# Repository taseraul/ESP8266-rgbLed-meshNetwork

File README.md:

# ESP8266-rgbLed-meshNetwork
Controller for RGB LED Strips linked in mesh network with ESP-Now protocol

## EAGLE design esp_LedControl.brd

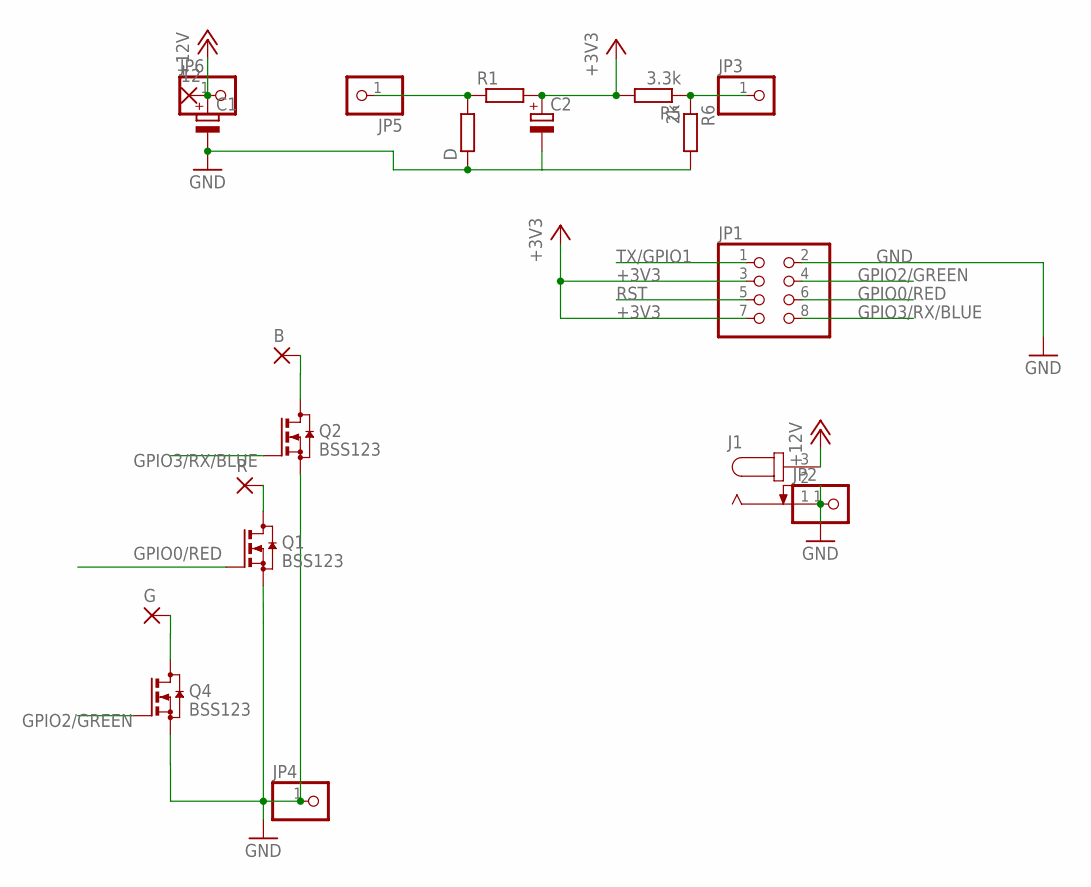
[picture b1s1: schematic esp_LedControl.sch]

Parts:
12: 3,17/1,3
B: 3,17/1,3
C1, C2: CPOL-EUE2.5-5; E2,5-5
D: R-EU_0204/7; 0204/7
G: 3,17/1,3
J1: JACK-PLUG0; SPC4077
JP1: PINHD-2X4; 2X04
JP2, JP3, JP4, JP5, JP6: PINHD-1X1; 1X01
Q1, Q2, Q4: BSS123; SOT23
R: 3,17/1,3
R1: R-EU_0204/7; 0204/7
R5: 3.3k; R0805
R6: 2k; R0805

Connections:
+3V3: C2.+, JP1.3, JP1.7, R1.2, R5.2
+12V: 12.1, C1.+, J1.3, JP6.1
GND: C1.-, C2.-, D.1, J1.1, J1.2, JP1.2, JP2.1, JP4.1, Q1.2 (S), Q2.2 (S), Q4.2 (S), R6.2
GPIO0/RED: JP1.6, Q1.1 (G)
GPIO2/GREEN: JP1.4, Q4.1 (G)
GPIO3/RX/BLUE: JP1.8, Q2.1 (G)
unnamed: G.1, Q4.3 (D)
unnamed: JP3.1, R5.1, R6.1
unnamed: B.1, Q2.3 (D)
unnamed: D.2, JP5.1, R1.1
unnamed: Q1.3 (D), R.1
RST: JP1.5
TX/GPIO1: JP1.1

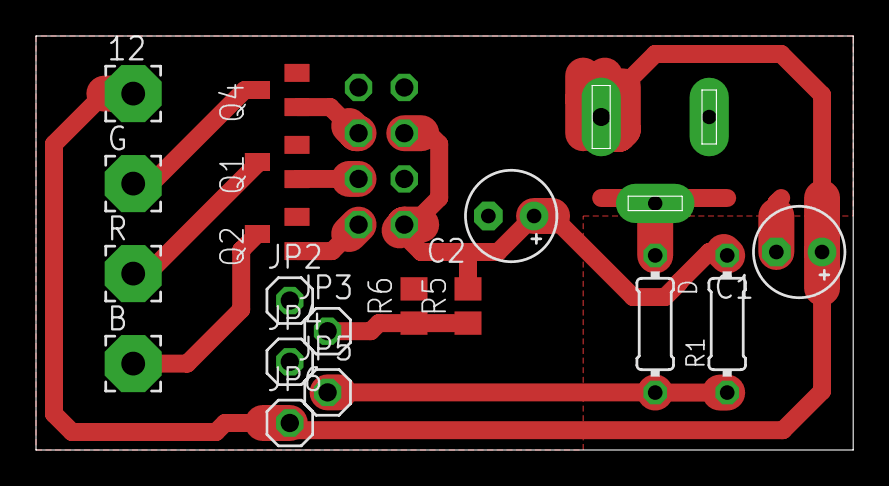
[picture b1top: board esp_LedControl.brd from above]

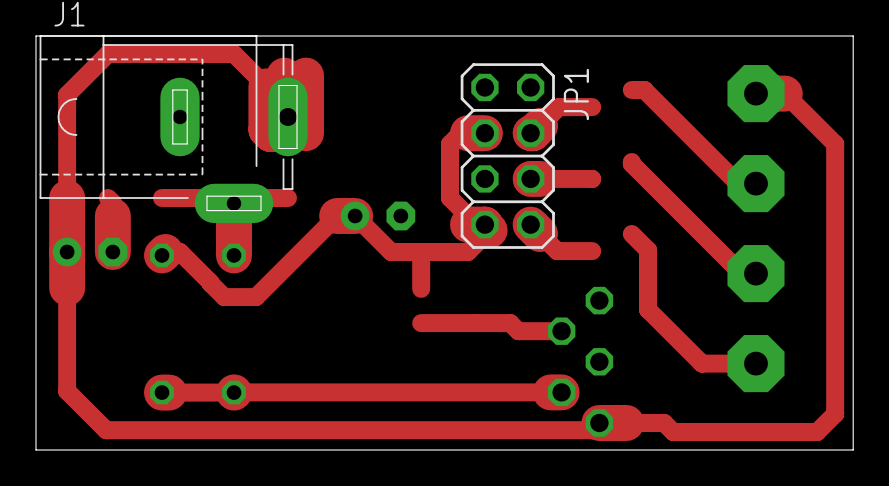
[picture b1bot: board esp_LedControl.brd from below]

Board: 2 copper layers, 45.4 x 23.0 mm, 20 parts (2 on the bottom side), 11 nets.

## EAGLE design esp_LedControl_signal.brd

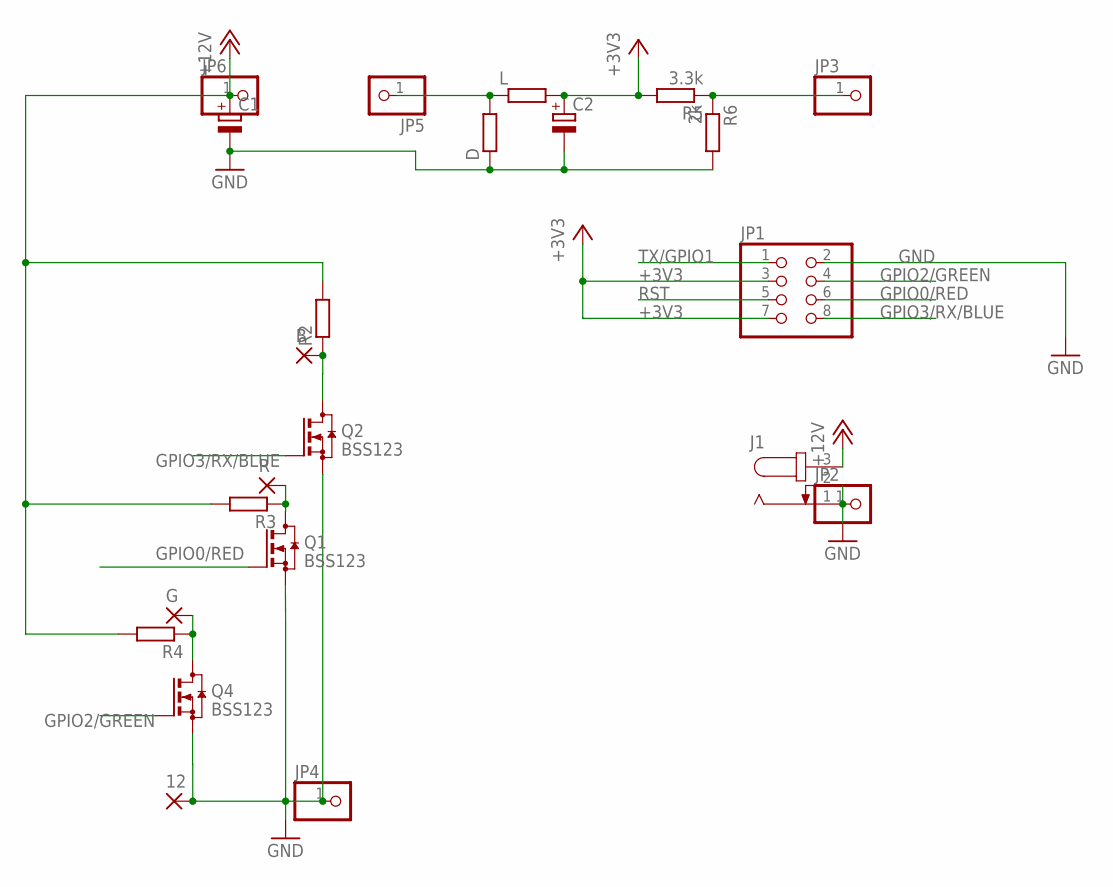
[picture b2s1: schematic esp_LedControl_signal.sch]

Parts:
12: 3,17/1,3
B: 3,17/1,3
C1, C2: CPOL-EUE2.5-5; E2,5-5
D: R-EU_0204/7; 0204/7
G: 3,17/1,3
J1: JACK-PLUG0; SPC4077
JP1: PINHD-2X4; 2X04
JP2, JP3, JP4, JP5, JP6: PINHD-1X1; 1X01
L: R-EU_0204/7; 0204/7
Q1, Q2, Q4: BSS123; SOT23
R: 3,17/1,3
R2, R3, R4: R-EU_R0805; R0805
R5: 3.3k; R1206
R6: 2k; R1206

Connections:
+3V3: C2.+, JP1.3, JP1.7, L.2, R5.2
+12V: C1.+, J1.3, JP6.1, R2.2, R3.2, R4.2
GND: 12.1, C1.-, C2.-, D.1, J1.1, J1.2, JP1.2, JP2.1, JP4.1, Q1.2 (S), Q2.2 (S), Q4.2 (S), R6.2
GPIO0/RED: JP1.6, Q1.1 (G)
GPIO2/GREEN: JP1.4, Q4.1 (G)
GPIO3/RX/BLUE: JP1.8, Q2.1 (G)
unnamed: G.1, Q4.3 (D), R4.1
unnamed: JP3.1, R5.1, R6.1
unnamed: B.1, Q2.3 (D), R2.1
unnamed: D.2, JP5.1, L.1
unnamed: Q1.3 (D), R.1, R3.1
RST: JP1.5
TX/GPIO1: JP1.1

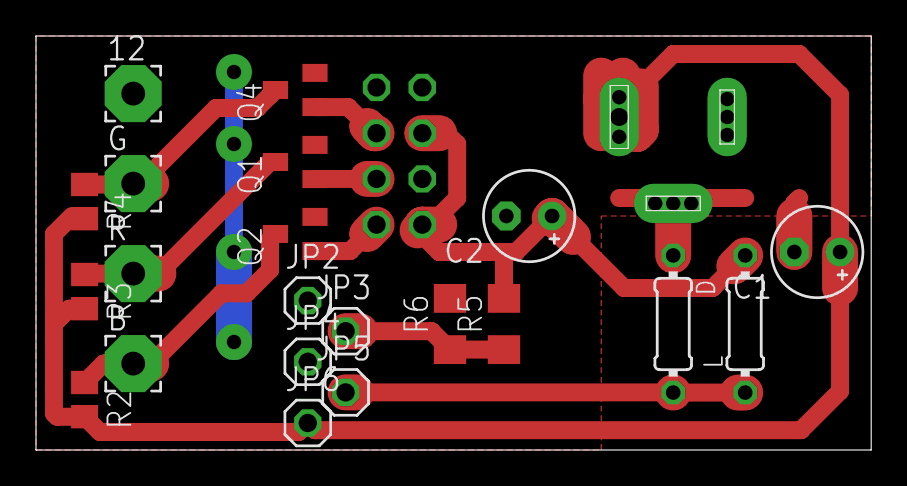
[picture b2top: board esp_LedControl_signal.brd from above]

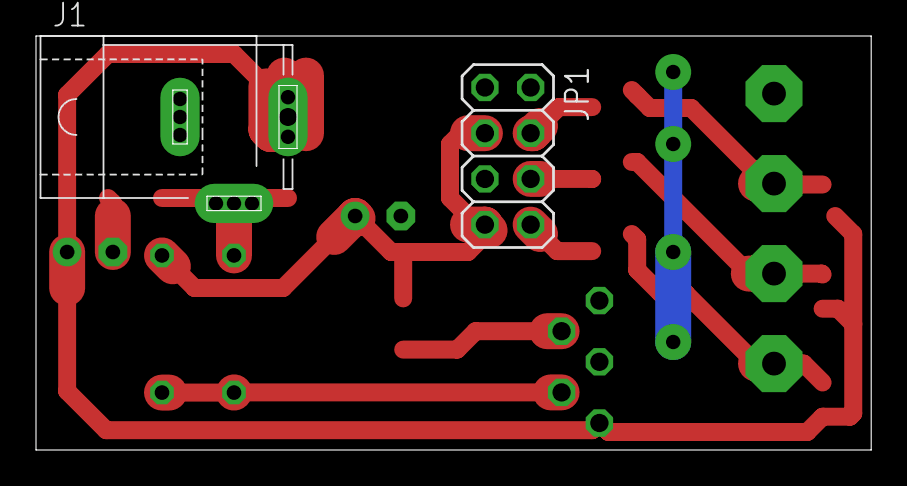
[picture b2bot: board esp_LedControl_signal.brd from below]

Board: 2 copper layers, 46.4 x 23.0 mm, 23 parts (2 on the bottom side), 11 nets.

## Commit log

2020-07-01 rename
2020-07-01 v2 animations WIP
2020-07-01 added .gitignore
2020-07-01 added comments
2020-07-01 added pcb boards
2020-07-06 switch to hue form RGB
2020-07-06 gitignore
2020-07-06 added HSL color cycling (master only)
2020-07-13 Static, fade and random strobe color animation
2020-07-20 fixes
